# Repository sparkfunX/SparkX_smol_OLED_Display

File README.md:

# SparkX smôl Header

[*SparkX smôl OLED Display (SPX-18996)*](https://www.sparkfun.com/products/18996)

The smôl OLED Display is a high contrast, small monochrome display with 128 x 32 pixels. Perfect for applications that don't possess a lot of space but still need to communicate to the user. The display uses the common SSD1306 driver IC fully supported by our blistering fast [SparkFun Qwiic OLED Library](https://github.com/sparkfun/SparkFun_Qwiic_OLED_Arduino_Library).

## Repository Contents

- **/Dosuments** - Driver datasheet
- **/Hardware** - Eagle design files
- **LICENSE.md** contains the licence information

## License Information

This product is _**open source**_!

Please review the LICENSE.md file for license information.

If you have any questions or concerns on licensing, please contact technical support on our [SparkFun forums](https://forum.sparkfun.com/viewforum.php?f=123).

Distributed as-is; no warranty is given.

- Your friends at SparkFun.

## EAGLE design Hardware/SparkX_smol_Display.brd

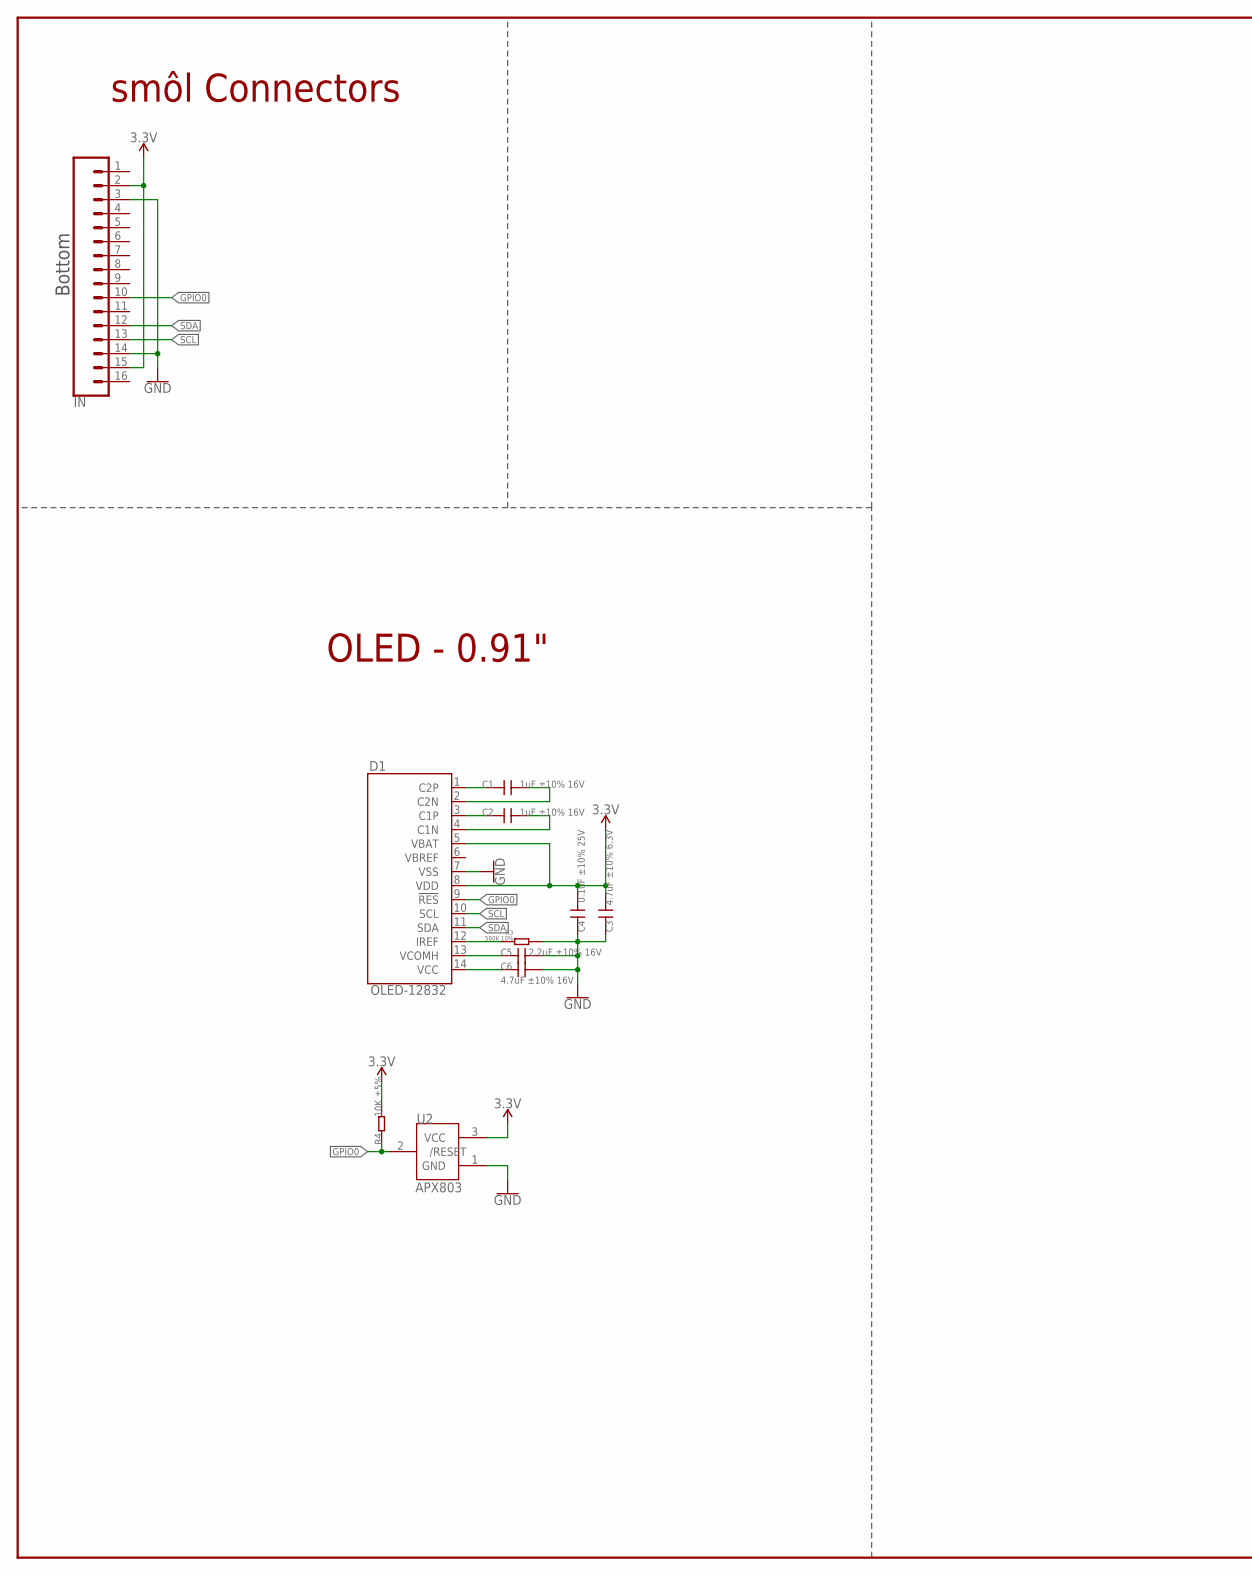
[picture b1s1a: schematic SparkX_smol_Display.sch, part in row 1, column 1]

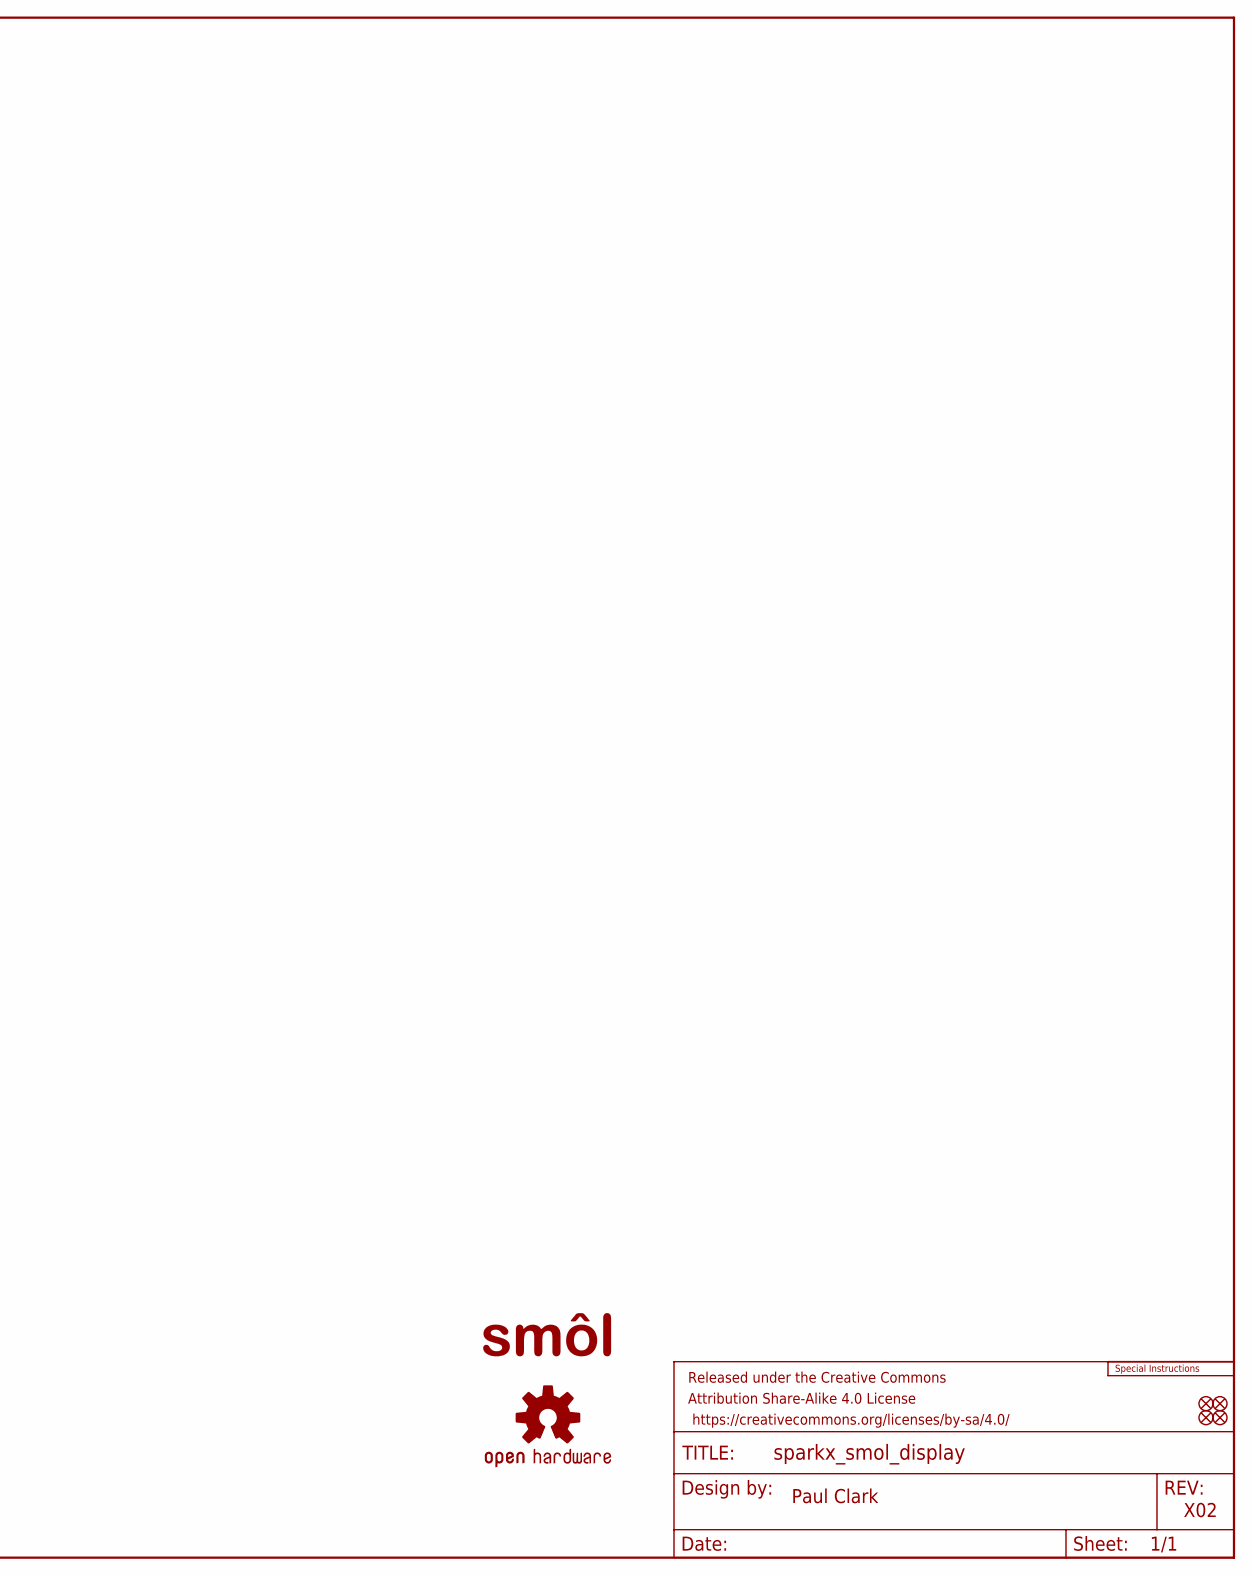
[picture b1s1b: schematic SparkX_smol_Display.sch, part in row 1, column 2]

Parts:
C1, C2: 1uF ±10% 16V; 0603
C3: 4.7uF ±10% 6.3V; 0603
C4: 0.1uF ±10% 25V; 0603
C5: 2.2uF ±10% 16V; 0603
C6: 4.7uF ±10% 16V; 0603
D1: OLED-12832
FD1, FD2, FD3, FD4: FIDUCIALUFIDUCIAL; FIDUCIAL-MICRO
FRAME1: FRAME-LEDGER; CREATIVE_COMMONS
IN: CONN_16FPC_16_0.5MM; FPC_16_0.5MM
LOGO1: SPECIAL_INSTRUCTIONS-ORDERING; ORDERING_INSTRUCTIONS
LOGO3: OSHW-LOGOMINI; OSHW-LOGO-MINI
R3: 560K 10%; 0603
R4: 10K ±5%; 0603
U2: APX803; SOT23
U$14: SMOL_LOGOSMALL; SMOL_SMALL

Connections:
3.3V: C3.1, C4.1, D1.5 (VBAT), D1.8 (VDD), IN.2, IN.15, R4.2, U2.3 (VCC)
GND: C3.2, C4.2, C5.2, C6.2, D1.7 (VSS), IN.3, IN.14, R3.1, U2.1 (GND)
GPIO0: D1.9 (!RES!), IN.10, R4.1, U2.2 (/RESET)
unnamed: C1.2, D1.1 (C2P)
unnamed: C1.1, D1.2 (C2N)
unnamed: C2.2, D1.3 (C1P)
unnamed: C2.1, D1.4 (C1N)
unnamed: C5.1, D1.13 (VCOMH)
unnamed: C6.1, D1.14 (VCC)
unnamed: D1.12 (IREF), R3.2
SCL: D1.10 (SCL), IN.13
SDA: D1.11 (SDA), IN.12

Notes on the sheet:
Paul Clark
X02
smôl Connectors
Bottom
OLED - 0.91"

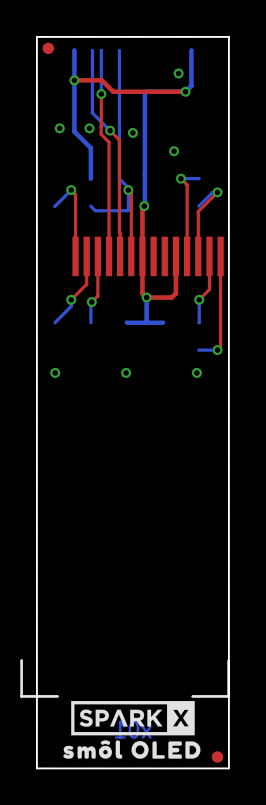
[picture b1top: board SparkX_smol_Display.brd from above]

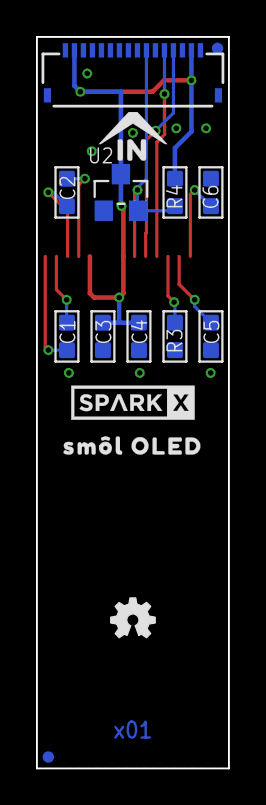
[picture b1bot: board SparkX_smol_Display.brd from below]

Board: 2 copper layers, 10.7 x 40.6 mm, 24 parts (17 on the bottom side), 12 nets.

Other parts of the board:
U$1, U$4: SM�L_OLED0
U$3, U$20: SPARKX-LOGO3; SPARKX-SMALL
U$12: IN0

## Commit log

2022-01-11 Add example and datasheet for display.
2022-03-24 Add docs. Add schematic.
2022-03-24 Add readme and ignore

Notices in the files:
parts and their libraries:
SparkFun-Aesthetics: Licensing: Creative Commons ShareAlike 4.0 International - https://creativecommons.org/licenses/by-sa/4.0
SparkFun-Aesthetics: Released under the Creative Commons Attribution Share-Alike 4.0 License
SparkFun-Aesthetics: https://creativecommons.org/licenses/by-sa/4.0
